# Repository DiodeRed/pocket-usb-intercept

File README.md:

# pocket-usb-intercept
A small mod board for the GDP Pocket to add a tiny internal USB hub for various purposes.

#### Bill of materials:

| Reference | Description                                   | Part Number            |
|-----------|-----------------------------------------------|------------------------|
| U1        | 4-port USB 2.0 Hub IC                         | CY7C65632-28LTXC       |
| Y1        | 12MHz Crystal                                 | ABM10-166-12.000MHZ-T3 |
| R4        | 649 resistor (0603, 1%)                       | (generic)              |
| R1,R3     | 10k resistor (0603, 1%)                       | (generic)              |
| R2        | 47k resistor (0603, 1%)                       | (generic)              |
| C3,C4     | 7pF capacitor (0603, 50V, NP0)                | CGA3E2NP01H070D080AA   |
| C5        | 1uF capacitor (0603, 25V, X7R)                | CL10B105KA8NNNC        |
| C1,C2     | 10uF capacitor (0805, 6.3V, X5R, low profile) | CL21A106MQCLNNC        |
| P1,P2     | Flat Flex Connector                           | FH19C-10S-0.5SH        |
|           | 10pos 0.5mm pitch 4cm Flex Cable              | 152660095              |
|           | PCB (16mm x 13mm x 0.4mm)                     |                        |

---

<br />This work is licensed under a <a rel="license" href="http://creativecommons.org/licenses/by-sa/4.0/">Creative Commons Attribution-ShareAlike 4.0 International License</a>.

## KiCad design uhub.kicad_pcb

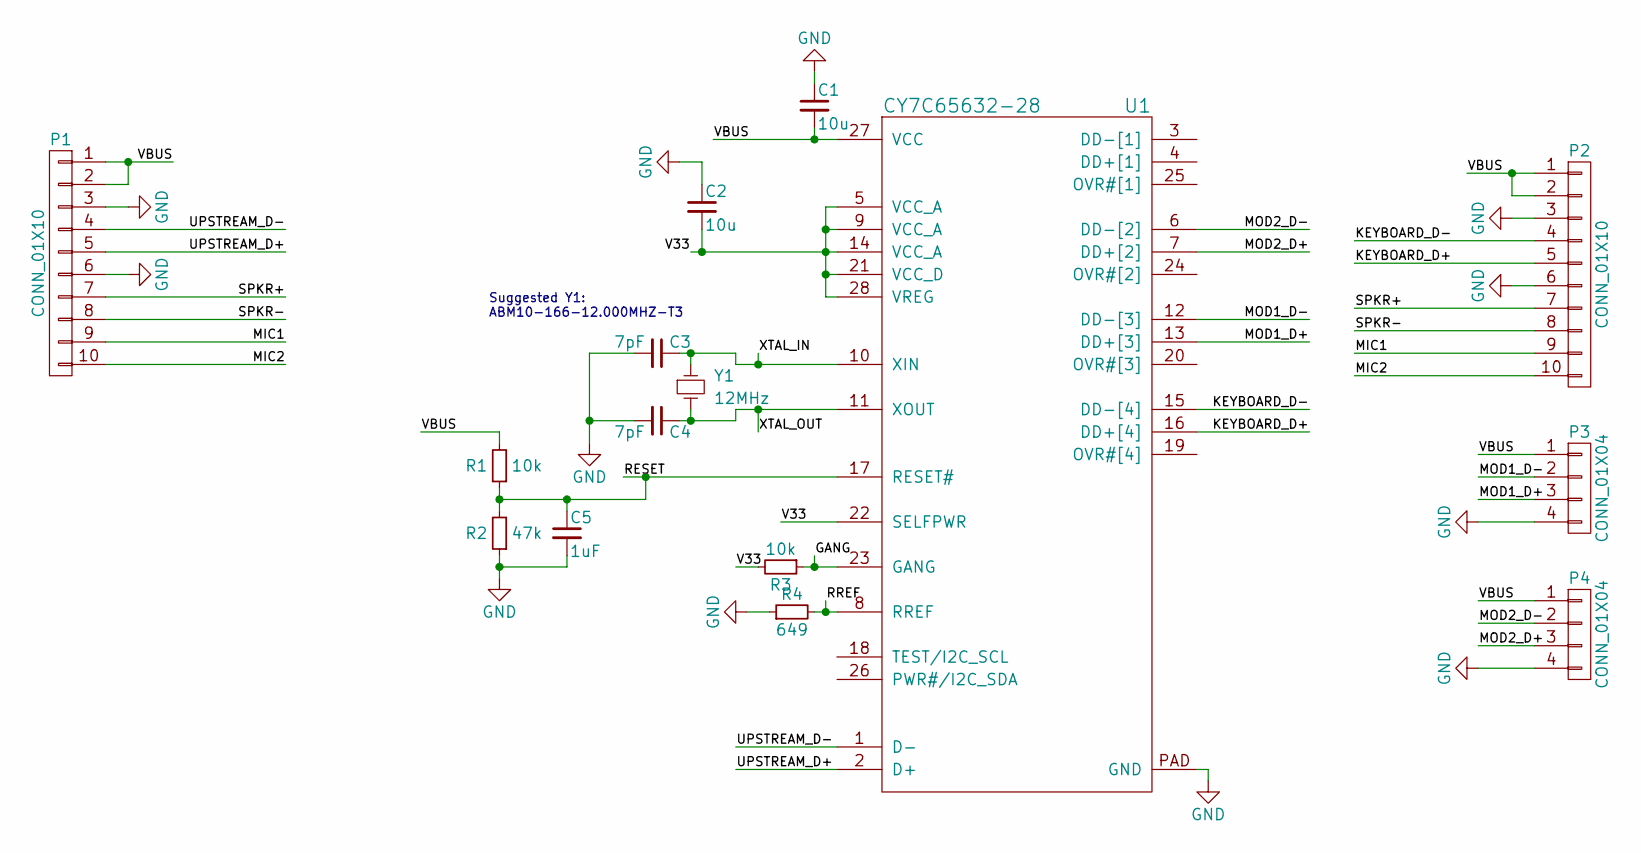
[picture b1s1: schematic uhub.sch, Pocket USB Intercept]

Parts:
C1, C2: 10u; C_0805
C3, C4: 7pF; C_0603
C5: 1uF; C_0603
P1: CONN_01X10; FH19C-10S-0.5SH
P2: CONN_01X10; FH19C-10S-0.5SH_REV
P3, P4: CONN_01X04; CONN-4-USB-TINY
R1, R3: 10k; R_0603
R2: 47k; R_0603
R4: 649; R_0603
U1: CY7C65632-28; QFN_28
Y1: 12MHz; ABM-XXX

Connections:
/GANG: R3.1, U1.23 (GANG)
/KEYBOARD_D+: P2.5, U1.16 (DD+[4])
/KEYBOARD_D-: P2.4, U1.15 (DD-[4])
/MIC1: P1.9, P2.9
/MIC2: P1.10, P2.10
/MOD1_D+: P3.3, U1.13 (DD+[3])
/MOD1_D-: P3.2, U1.12 (DD-[3])
/MOD2_D+: P4.3, U1.7 (DD+[2])
/MOD2_D-: P4.2, U1.6 (DD-[2])
/RESET: C5.1, R1.1, R2.2, U1.17 (RESET#)
/RREF: R4.2, U1.8 (RREF)
/SPKR+: P1.7, P2.7
/SPKR-: P1.8, P2.8
/UPSTREAM_D+: P1.5, U1.2 (D+)
/UPSTREAM_D-: P1.4, U1.1 (D-)
/V33: C2.2, R3.2, U1.5 (VCC_A), U1.9 (VCC_A), U1.14 (VCC_A), U1.21 (VCC_D), U1.22 (SELFPWR), U1.28 (VREG)
/VBUS: C1.2, P1.1, P1.2, P2.1, P2.2, P3.1, P4.1, R1.2, U1.27 (VCC)
/XTAL_IN: C3.1, U1.10 (XIN), Y1.1
/XTAL_OUT: C4.1, U1.11 (XOUT), Y1.2
GND: C1.1, C2.1, C3.2, C4.2, C5.2, P1.3, P1.6, P2.3, P2.6, P3.4, P4.4, R2.1, R4.1, U1.PAD (GND)

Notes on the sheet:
Suggested Y1: ABM10-166-12.000MHZ-T3

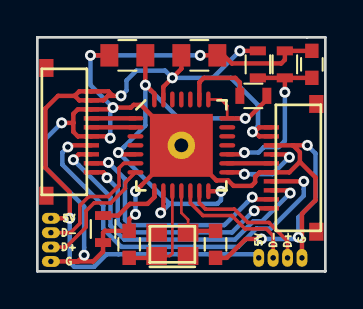
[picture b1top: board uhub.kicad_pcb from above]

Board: 2 copper layers, 16.0 x 13.0 mm, 15 parts (0 on the bottom side), 20 nets.

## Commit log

2017-10-10 Commit files
